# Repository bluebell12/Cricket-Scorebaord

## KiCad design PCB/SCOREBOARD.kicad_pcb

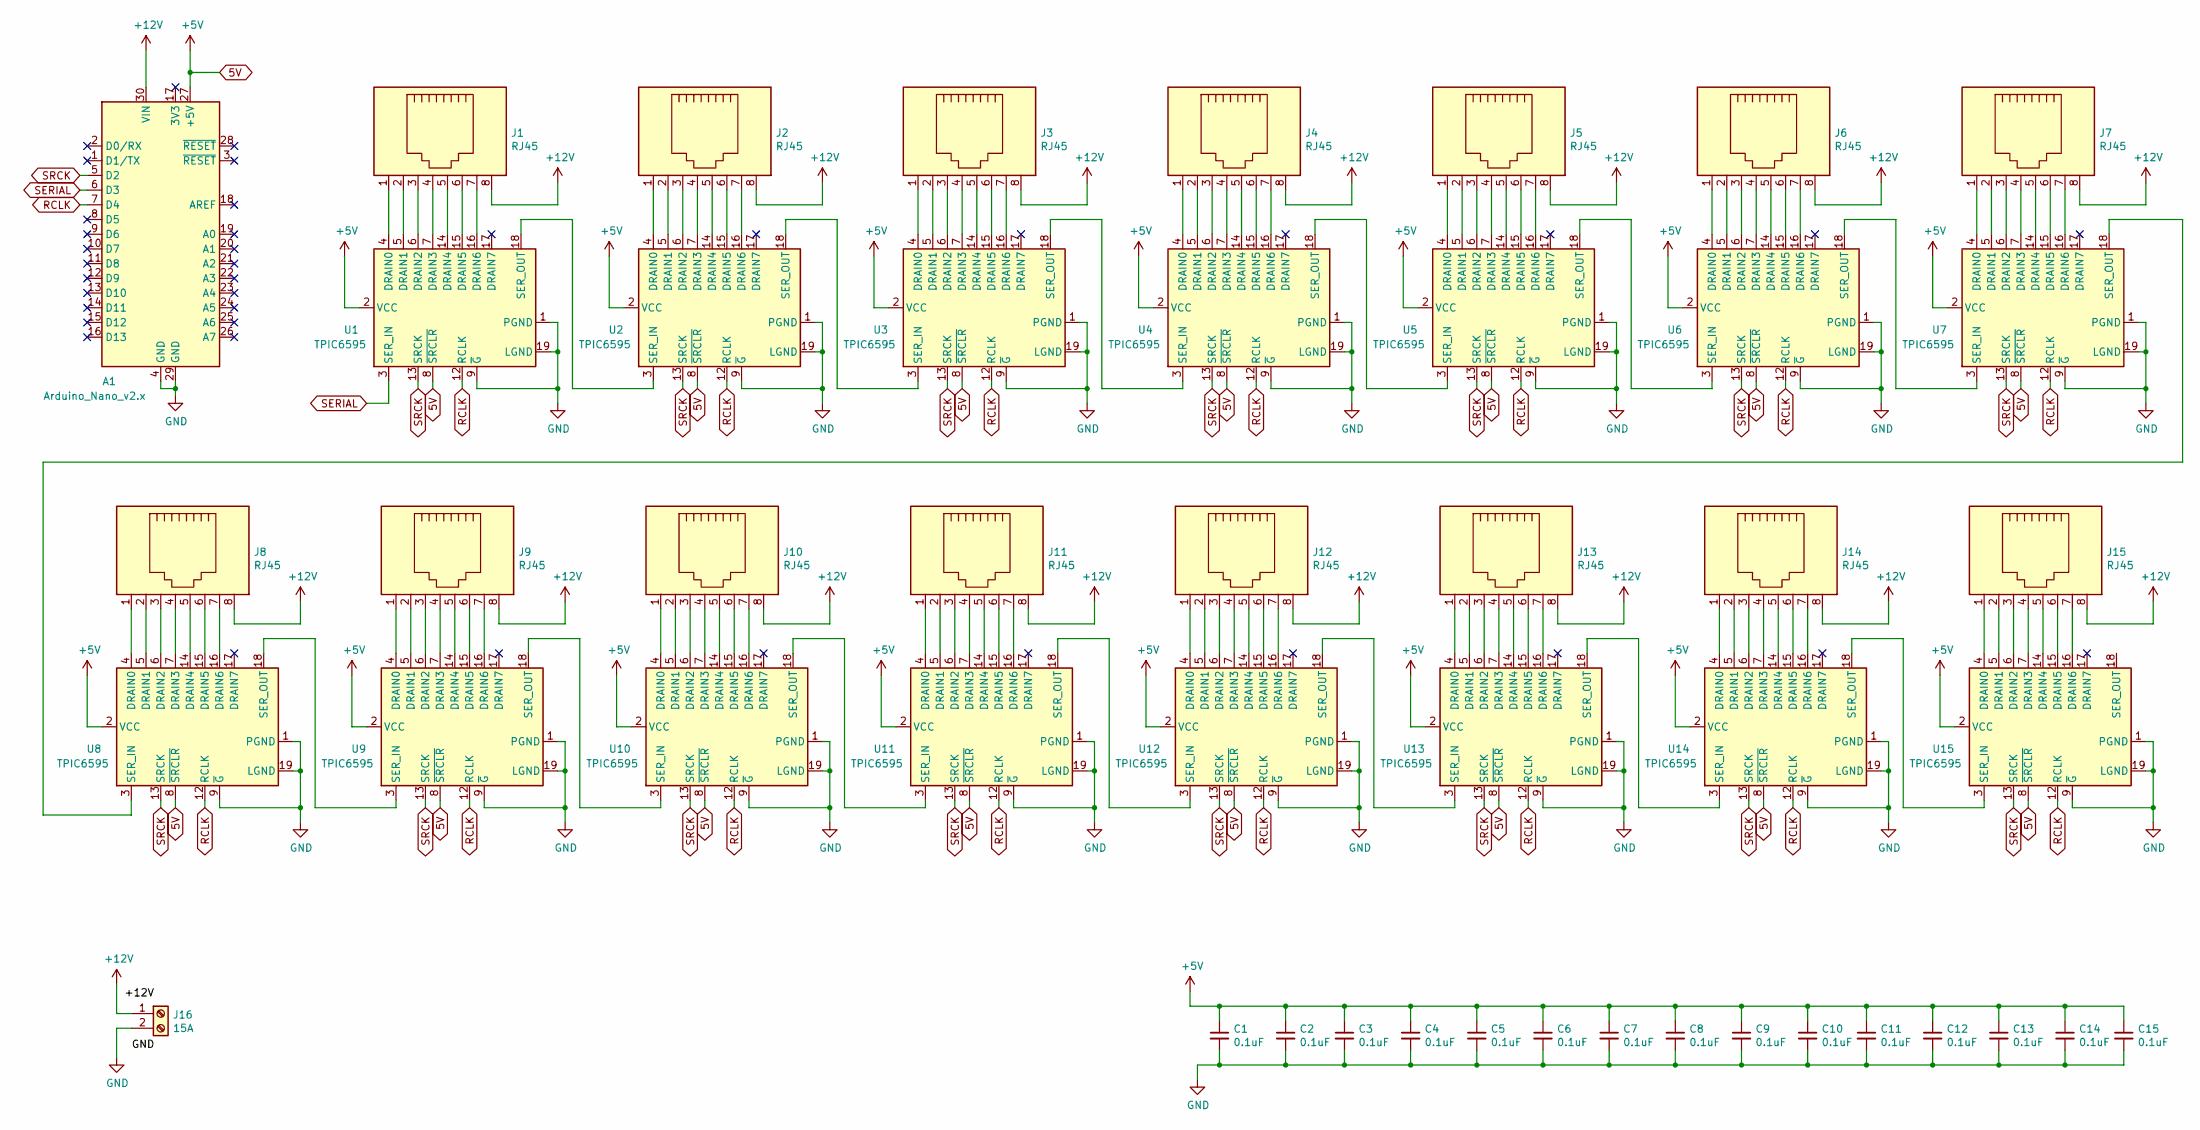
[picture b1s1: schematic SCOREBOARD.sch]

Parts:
A1: Arduino_Nano_v2.x; Arduino_Nano
C1, C2, C3, C4, C5, C6, C7, C8, C9, C10, C11, C12, C13, C14, C15: 0.1uF; C_Disc_D7.0mm_W2.5mm_P5.00mm
J1, J2, J3, J4, J5, J6, J7, J8, J9, J10, J11, J12, J13, J14, J15: RJ45; RJ45_Ninigi_GE
J16: 15A; Power Terminal
U1, U2, U3, U4, U5, U6, U7, U8, U9, U10, U11, U12, U13, U14, U15: TPIC6595; DIP-20_W7.62mm

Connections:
5V: A1.27 (+5V), C1.1, C2.1, C3.1, C4.1, C5.1, C6.1, C7.1, C8.1, C9.1, C10.1, C11.1, C12.1, C13.1, C14.1, C15.1, U1.2 (VCC), U1.8 (~SRCLR), U2.2 (VCC), U2.8 (~SRCLR), U3.2 (VCC), U3.8 (~SRCLR), U4.2 (VCC), U4.8 (~SRCLR), U5.2 (VCC), U5.8 (~SRCLR), U6.2 (VCC), U6.8 (~SRCLR), U7.2 (VCC), U7.8 (~SRCLR), U8.2 (VCC), U8.8 (~SRCLR), U9.2 (VCC), U9.8 (~SRCLR), U10.2 (VCC), U10.8 (~SRCLR), U11.2 (VCC), U11.8 (~SRCLR), U12.2 (VCC), U12.8 (~SRCLR), U13.2 (VCC), U13.8 (~SRCLR), U14.2 (VCC), U14.8 (~SRCLR), U15.2 (VCC), U15.8 (~SRCLR)
+12V: A1.30 (VIN), J1.8, J2.8, J3.8, J4.8, J5.8, J6.8, J7.8, J8.8, J9.8, J10.8, J11.8, J12.8, J13.8, J14.8, J15.8, J16.1
GND: A1.4 (GND), A1.29 (GND), C1.2, C2.2, C3.2, C4.2, C5.2, C6.2, C7.2, C8.2, C9.2, C10.2, C11.2, C12.2, C13.2, C14.2, C15.2, J16.2, U1.1 (PGND), U1.9 (~G), U1.10 (PGND), U1.11 (PGND), U1.19 (LGND), U1.20 (PGND), U2.1 (PGND), U2.9 (~G), U2.10 (PGND), U2.11 (PGND), U2.19 (LGND), U2.20 (PGND), U3.1 (PGND), U3.9 (~G), U3.10 (PGND), U3.11 (PGND), U3.19 (LGND), U3.20 (PGND), U4.1 (PGND), U4.9 (~G), U4.10 (PGND), U4.11 (PGND), U4.19 (LGND), U4.20 (PGND), U5.1 (PGND), U5.9 (~G), U5.10 (PGND), U5.11 (PGND), U5.19 (LGND), U5.20 (PGND), U6.1 (PGND), U6.9 (~G), U6.10 (PGND), U6.11 (PGND), U6.19 (LGND), U6.20 (PGND), U7.1 (PGND), U7.9 (~G), U7.10 (PGND), U7.11 (PGND), U7.19 (LGND), U7.20 (PGND), U8.1 (PGND), U8.9 (~G), U8.10 (PGND), U8.11 (PGND), U8.19 (LGND), U8.20 (PGND), U9.1 (PGND), U9.9 (~G), U9.10 (PGND), U9.11 (PGND), U9.19 (LGND), U9.20 (PGND), U10.1 (PGND), U10.9 (~G), U10.10 (PGND), U10.11 (PGND), U10.19 (LGND), U10.20 (PGND), U11.1 (PGND), U11.9 (~G), U11.10 (PGND), U11.11 (PGND), U11.19 (LGND), U11.20 (PGND), U12.1 (PGND), U12.9 (~G), U12.10 (PGND), U12.11 (PGND), U12.19 (LGND), U12.20 (PGND), U13.1 (PGND), U13.9 (~G), U13.10 (PGND), U13.11 (PGND), U13.19 (LGND), U13.20 (PGND), U14.1 (PGND), U14.9 (~G), U14.10 (PGND), U14.11 (PGND), U14.19 (LGND), U14.20 (PGND), U15.1 (PGND), U15.9 (~G), U15.10 (PGND), U15.11 (PGND), U15.19 (LGND), U15.20 (PGND)
unnamed: J1.1, U1.4 (DRAIN0)
unnamed: J1.2, U1.5 (DRAIN1)
unnamed: J1.3, U1.6 (DRAIN2)
unnamed: J1.4, U1.7 (DRAIN3)
unnamed: J1.5, U1.14 (DRAIN4)
unnamed: J1.6, U1.15 (DRAIN5)
unnamed: J1.7, U1.16 (DRAIN6)
unnamed: J2.1, U2.4 (DRAIN0)
unnamed: J2.2, U2.5 (DRAIN1)
unnamed: J2.3, U2.6 (DRAIN2)
unnamed: J2.4, U2.7 (DRAIN3)
unnamed: J2.5, U2.14 (DRAIN4)
unnamed: J2.6, U2.15 (DRAIN5)
unnamed: J2.7, U2.16 (DRAIN6)
unnamed: J3.1, U3.4 (DRAIN0)
unnamed: J3.2, U3.5 (DRAIN1)
unnamed: J3.3, U3.6 (DRAIN2)
unnamed: J3.4, U3.7 (DRAIN3)
unnamed: J3.5, U3.14 (DRAIN4)
unnamed: J3.6, U3.15 (DRAIN5)
unnamed: J3.7, U3.16 (DRAIN6)
unnamed: J4.1, U4.4 (DRAIN0)
unnamed: J4.2, U4.5 (DRAIN1)
unnamed: J4.3, U4.6 (DRAIN2)
unnamed: J4.4, U4.7 (DRAIN3)
unnamed: J4.5, U4.14 (DRAIN4)
unnamed: J4.6, U4.15 (DRAIN5)
unnamed: J4.7, U4.16 (DRAIN6)
unnamed: J5.1, U5.4 (DRAIN0)
unnamed: J5.2, U5.5 (DRAIN1)
unnamed: J5.3, U5.6 (DRAIN2)
unnamed: J5.4, U5.7 (DRAIN3)
unnamed: J5.5, U5.14 (DRAIN4)
unnamed: J5.6, U5.15 (DRAIN5)
unnamed: J5.7, U5.16 (DRAIN6)
unnamed: J6.1, U6.4 (DRAIN0)
unnamed: J6.2, U6.5 (DRAIN1)
unnamed: J6.3, U6.6 (DRAIN2)
unnamed: J6.4, U6.7 (DRAIN3)
unnamed: J6.5, U6.14 (DRAIN4)
unnamed: J6.6, U6.15 (DRAIN5)
unnamed: J6.7, U6.16 (DRAIN6)
unnamed: J7.1, U7.4 (DRAIN0)
unnamed: J7.2, U7.5 (DRAIN1)
unnamed: J7.3, U7.6 (DRAIN2)
unnamed: J7.4, U7.7 (DRAIN3)
unnamed: J7.5, U7.14 (DRAIN4)
unnamed: J7.6, U7.15 (DRAIN5)
unnamed: J7.7, U7.16 (DRAIN6)
unnamed: J8.1, U8.4 (DRAIN0)
unnamed: J8.2, U8.5 (DRAIN1)
unnamed: J8.3, U8.6 (DRAIN2)
unnamed: J8.4, U8.7 (DRAIN3)
unnamed: J8.5, U8.14 (DRAIN4)
unnamed: J8.6, U8.15 (DRAIN5)
unnamed: J8.7, U8.16 (DRAIN6)
unnamed: J9.1, U9.4 (DRAIN0)
unnamed: J9.2, U9.5 (DRAIN1)
unnamed: J9.3, U9.6 (DRAIN2)
unnamed: J9.4, U9.7 (DRAIN3)
unnamed: J9.5, U9.14 (DRAIN4)
unnamed: J9.6, U9.15 (DRAIN5)
unnamed: J9.7, U9.16 (DRAIN6)
unnamed: J10.1, U10.4 (DRAIN0)
unnamed: J10.2, U10.5 (DRAIN1)
unnamed: J10.3, U10.6 (DRAIN2)
unnamed: J10.4, U10.7 (DRAIN3)
unnamed: J10.5, U10.14 (DRAIN4)
unnamed: J10.6, U10.15 (DRAIN5)
unnamed: J10.7, U10.16 (DRAIN6)
unnamed: J11.1, U11.4 (DRAIN0)
unnamed: J11.2, U11.5 (DRAIN1)
unnamed: J11.3, U11.6 (DRAIN2)
unnamed: J11.4, U11.7 (DRAIN3)
unnamed: J11.5, U11.14 (DRAIN4)
unnamed: J11.6, U11.15 (DRAIN5)
unnamed: J11.7, U11.16 (DRAIN6)
unnamed: J12.1, U12.4 (DRAIN0)
unnamed: J12.2, U12.5 (DRAIN1)
unnamed: J12.3, U12.6 (DRAIN2)
unnamed: J12.4, U12.7 (DRAIN3)
unnamed: J12.5, U12.14 (DRAIN4)
unnamed: J12.6, U12.15 (DRAIN5)
unnamed: J12.7, U12.16 (DRAIN6)
unnamed: J13.1, U13.4 (DRAIN0)
unnamed: J13.2, U13.5 (DRAIN1)
unnamed: J13.3, U13.6 (DRAIN2)
unnamed: J13.4, U13.7 (DRAIN3)
unnamed: J13.5, U13.14 (DRAIN4)
unnamed: J13.6, U13.15 (DRAIN5)
unnamed: J13.7, U13.16 (DRAIN6)
unnamed: J14.1, U14.4 (DRAIN0)
unnamed: J14.2, U14.5 (DRAIN1)
unnamed: J14.3, U14.6 (DRAIN2)
unnamed: J14.4, U14.7 (DRAIN3)
unnamed: J14.5, U14.14 (DRAIN4)
unnamed: J14.6, U14.15 (DRAIN5)
unnamed: J14.7, U14.16 (DRAIN6)
unnamed: J15.1, U15.4 (DRAIN0)
unnamed: J15.2, U15.5 (DRAIN1)
unnamed: J15.3, U15.6 (DRAIN2)
unnamed: J15.4, U15.7 (DRAIN3)
unnamed: J15.5, U15.14 (DRAIN4)
unnamed: J15.6, U15.15 (DRAIN5)
unnamed: J15.7, U15.16 (DRAIN6)
unnamed: U1.18 (SER_OUT), U2.3 (SER_IN)
unnamed: U2.18 (SER_OUT), U3.3 (SER_IN)
unnamed: U3.18 (SER_OUT), U4.3 (SER_IN)
unnamed: U4.18 (SER_OUT), U5.3 (SER_IN)
unnamed: U5.18 (SER_OUT), U6.3 (SER_IN)
unnamed: U6.18 (SER_OUT), U7.3 (SER_IN)
unnamed: U7.18 (SER_OUT), U8.3 (SER_IN)
unnamed: U8.18 (SER_OUT), U9.3 (SER_IN)
unnamed: U9.18 (SER_OUT), U10.3 (SER_IN)
unnamed: U10.18 (SER_OUT), U11.3 (SER_IN)
unnamed: U11.18 (SER_OUT), U12.3 (SER_IN)
unnamed: U12.18 (SER_OUT), U13.3 (SER_IN)
unnamed: U13.18 (SER_OUT), U14.3 (SER_IN)
unnamed: U14.18 (SER_OUT), U15.3 (SER_IN)
RCLK: A1.7 (D4), U1.12 (RCLK), U2.12 (RCLK), U3.12 (RCLK), U4.12 (RCLK), U5.12 (RCLK), U6.12 (RCLK), U7.12 (RCLK), U8.12 (RCLK), U9.12 (RCLK), U10.12 (RCLK), U11.12 (RCLK), U12.12 (RCLK), U13.12 (RCLK), U14.12 (RCLK), U15.12 (RCLK)
SERIAL: A1.6 (D3), U1.3 (SER_IN)
SRCK: A1.5 (D2), U1.13 (SRCK), U2.13 (SRCK), U3.13 (SRCK), U4.13 (SRCK), U5.13 (SRCK), U6.13 (SRCK), U7.13 (SRCK), U8.13 (SRCK), U9.13 (SRCK), U10.13 (SRCK), U11.13 (SRCK), U12.13 (SRCK), U13.13 (SRCK), U14.13 (SRCK), U15.13 (SRCK)

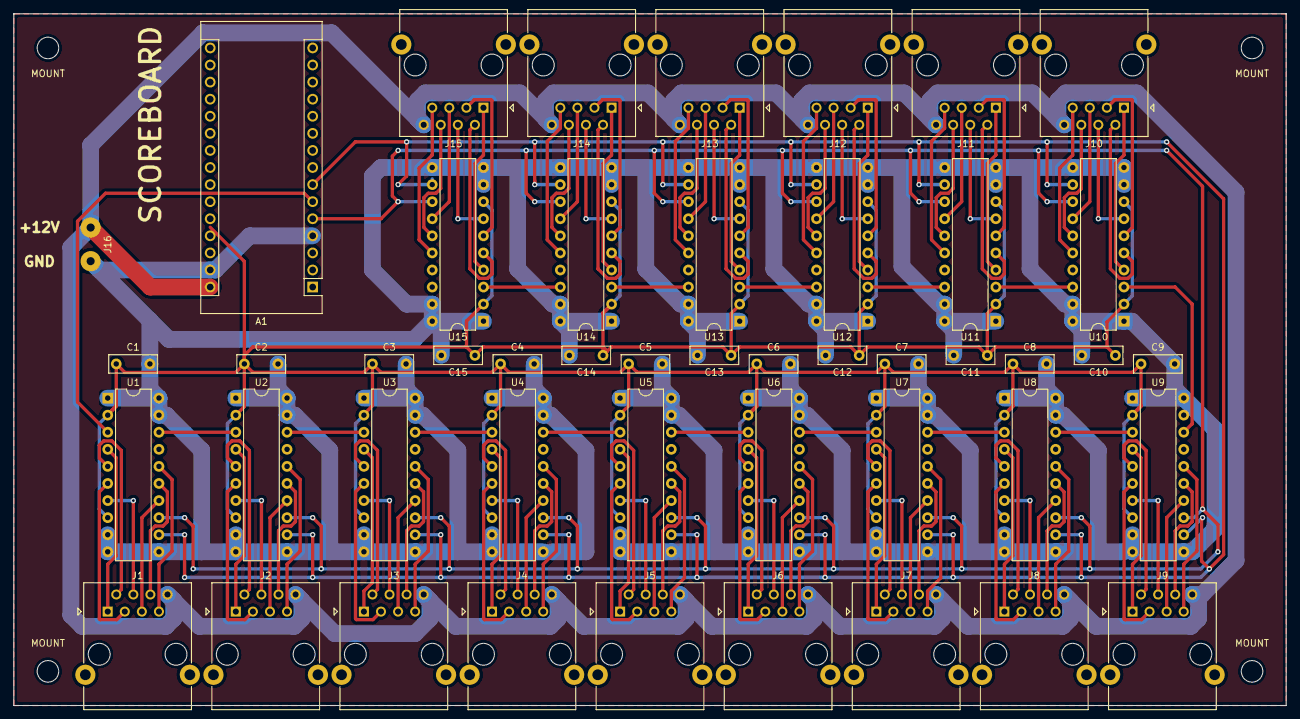
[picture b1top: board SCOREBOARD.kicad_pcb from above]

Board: 2 copper layers, 189.2 x 102.9 mm, 51 parts (0 on the bottom side), 125 nets.

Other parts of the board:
MOUNT: HOLE; MountingHole_3.2mm_M3
MOUNT#2, MOUNT#3, MOUNT#4: HOLE; MountingHole_3.2mm_M3

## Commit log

2021-12-15 Initial commit of PCB
    KICAD schematic and PCB design
2022-01-17 First complete CAD of digit
    First digit design and export of parts for 3D printing.
2022-05-01 Updates to CAD design plus initial (untested) effort at creating a console test app to send commands to Arduino cycle through numbers on each digit to allow quick testing.
